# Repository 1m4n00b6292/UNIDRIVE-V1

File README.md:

# UNIDRIVE V1

A compact brushed DC motor driver board with encoder feedback, shunt current sensing and CAN bus, controlled by an **STM32G431KBU6**.

> ⚠️ **Status: hardware V1 done, firmware under development.**
> The firmware has not been checked on real hardware yet. Nothing in the firmware sections below should be read as tested or working.

## Overview

**UNIDRIVE** is a single-channel brushed DC motor driver built around the **TI DRV8701P** gate driver and an H-bridge made of 4 discrete N-channel MOSFETs. An **STM32G431KBU6** (Cortex-M4F, 170 MHz) handles the control. Feedback comes from:

- a **quadrature encoder** for speed and position
- a **5 mΩ low-side shunt** read through the DRV8701 current-sense amplifier

The board can be commanded over **CAN (FDCAN1)** or **UART**, and four status LEDs show its state.

The goal is a small, general-purpose driver for robotics and hobby projects, with duty, current, velocity and position control modes.

<!-- Fixed width, centered -->
<p align="center">
  
  <br>
  <em>Figure 1: PCB 3D view (top)</em>
</p>

## Main Components

### Hardware

| Part | Function |
|------|----------|
| STM32G431KBU6 (UFQFPN-32) + 24 MHz crystal | Main MCU (HSE → PLL 170 MHz) |
| DRV8701P | Brushed DC H-bridge gate driver (PWM IN1/IN2 variant) |
| 4 × N-channel MOSFET | Full H-bridge power stage |
| 5 mΩ shunt (R8) | Current sensing, read through the DRV8701 SO amplifier (gain 20 V/V) |
| Quadrature encoder (external) | Speed / position feedback (x4 decoding on TIM2) |
| TJA1051T/3 | CAN transceiver, with optional 120 Ω termination (JP2) |
| AP2112K-3.3 | 3.3 V LDO for the MCU |
| 4 LEDs | RUN / CAL / FAULT / COMM status |
| SWD header (J6) | Programming and debugging |

### Pin Map

| Signal | Pin | Peripheral | Notes |
|--------|-----|------------|-------|
| HSE OSC_IN / OSC_OUT | PF0 / PF1 | RCC | 24 MHz crystal |
| CSENSE (DRV8701 SO) | PA0 | ADC1_IN1 | Current-sense amplifier output |
| nFAULT | PA1 | GPIO / EXTI1 | Pull-up to DVDD, active low |
| IN1 / IN2 | PA2 / PA3 | TIM15_CH1 / CH2 | 20 kHz PWM |
| nSLEEP | PA4 | GPIO | Driver enable |
| UART TX / RX | PA9 / PA10 | USART1 | On header J5 |
| CAN RX / TX | PA11 / PA12 | FDCAN1 | To TJA1051T/3 |
| SWDIO / SWCLK | PA13 / PA14 | SWD | Header J6 |
| Encoder A / B | PA15 / PB3 | TIM2_CH1 / CH2 | 32-bit encoder counter |
| LED RUN / CAL / FAULT / COMM | PB4 / PB5 / PB6 / PB7 | GPIO | Active low |
| BOOT0 | PB8 | — | 10k to GND (boot from flash) |
| Expansion | PA5, PA6, PA7, PA8, PB0 | — | Free, on header J5 |

<!-- Fixed width, centered -->
<p align="center">
  
  <br>
  <em>Figure 2: Layout view (L1)</em>
</p>
<p align="center">
  
  <br>
  <em>Figure 3: Layout view (L2)</em>
</p>
<p align="center">
  
  <br>
  <em>Figure 4: Layout view (L3)</em>
</p>
<p align="center">
  
  <br>
  <em>Figure 5: Layout view (L4)</em>
</p>

### Connectors

| Connector | Pinout |
|-----------|--------|
| **J1** (1×12) | 1/3 CANL, 2/4 CANH, 5 VENC, 6 ENCA, 7 ENCB, 8 GND, 9 M−, 10 M+, 11 GND, 12 VCC (power input) |
| **J2** (1×3) | Encoder supply select: +5 V (1-2) or +3.3 V (2-3) |
| **J5** (2×4) | PA9 (TX), PA10 (RX), GND, PA8, PB0, PA7, PA6, PA5 |
| **J6** (1×3) | SWDIO, SWCLK, GND |

> **JP1** connects the TJA1051 VIO pin to +3.3 V. It is an **open** solder jumper by default and **must be bridged** for CAN to work.
> **JP2** enables the 120 Ω CAN termination. Bridge it only on the boards at the ends of the bus.

### Driver Logic (DRV8701P)

| IN1 | IN2 | Bridge state |
|-----|-----|--------------|
| 0 | 0 | Coast (Hi-Z) |
| 1 | 0 | Forward |
| 0 | 1 | Reverse |
| 1 | 1 | Brake (low-side slow decay) |

- Current scaling: `I ≈ (V_SO − 0.05 V) / (0.005 Ω × 20)` ≈ **10 A/V**
- The SO output is valid only while the bridge is driving, not during brake or coast.
- Hardware current chopping limit: VREF ≈ 2.09 V → about **20 A**

## Firmware

> 🚧 **Under development.** The firmware structure and features below are the design target. They have been written and partly simulated on a PC, but **not yet confirmed on the real board**.

The firmware is built with **STM32CubeMX + CMake + STM32 HAL (G4)**. CubeMX generates the pin setup and peripheral init. All application code is in `App/`, and `main.c` only calls `app_init()` and `app_update()`.

### Planned Software Modules

| Layer / File | Description | Status |
|--------------|-------------|--------|
| `App/config.h` | Single place for every tunable value (PWM frequency, gains, limits, motor model) | 🚧 In progress |
| `App/bsp/` | Low-level peripheral drivers: GPIO/LEDs, TIM15 PWM, ADC + DMA, TIM2 encoder, TIM6 tick, USART1 DMA, FDCAN | 🚧 Written, not verified on hardware |
| `App/sensor/current` | Shunt current measurement synced to the PWM, offset calibration, filtering, overcurrent detection | 🚧 Written, not verified on hardware |
| `App/sensor/encoder` | Position (64-bit) and velocity estimation (PLL observer) | 🚧 Written, not verified on hardware |
| `App/sensor/monitor` | VDDA and MCU temperature monitoring | 🚧 Written, not verified on hardware |
| `App/control/drv8701` | Driver state machine: sleep / wake / ready / fault handling | 🚧 Written, not verified on hardware |
| `App/control/hbridge` | Duty → DRV8701P switching pattern, ADC sample timing | 🚧 Written, not verified on hardware |
| `App/control/pid`, `profile` | PID controller (ported from VIXULY), trapezoidal motion profile | 🚧 Written, not verified on hardware |
| `App/control/control` | Control loops: duty, current, velocity and position modes, fault handling | 🚧 Written, not verified on hardware |
| `App/app/` | State machine, CLI, telemetry, CAN protocol, parameter storage in flash | ⏳ Not started |

### Planned Features

- [ ] Control modes: **OFF / BRAKE / DUTY / CURRENT / VELOCITY / POSITION**
- [ ] 20 kHz PWM with current sampling locked to the PWM period
- [ ] Velocity PID with feed-forward and setpoint ramp
- [ ] Position control with a trapezoidal motion profile
- [ ] Software overcurrent, stall, following-error and over-temperature protection
- [ ] DRV8701 fault handling (nFAULT)
- [ ] UART command line and telemetry
- [ ] CAN protocol with node addressing
- [ ] Parameter storage in flash

### Development Progress

- [x] Schematic and PCB (V1)
- [x] Pin map and peripheral plan
- [x] Firmware architecture
- [x] Low-level drivers and control code written
- [x] Control logic tested in a PC simulation (motor + bridge + encoder model)
- [ ] **Board bring-up on real hardware**
- [ ] Current-sense calibration on hardware
- [ ] PID tuning on a real motor
- [ ] Application layer (CLI, CAN protocol, flash parameters)

## Quick User Guide

> The steps below describe the intended workflow. They may change as the firmware develops.

### 1. Build and flash

1. Open the firmware project (CMake, generated by STM32CubeMX).
2. Review `App/config.h`, especially the motor model, encoder resolution and current limits.
3. Build and flash through the **SWD header (J6)** with an ST-Link or a similar probe.

### 2. Hardware setup

1. Bridge **JP1** if you want to use CAN.
2. Set **J2** to match your encoder supply voltage (5 V or 3.3 V).
3. Connect the motor to **M+ / M−**, the encoder to **ENCA / ENCB / VENC / GND**, and the supply to **VCC / GND** on J1.
4. Connect a USB-UART adapter to **J5** (PA9 TX, PA10 RX, GND) for the debug terminal.

### 3. Run

🚧 *Under development: the command interface and CAN protocol are not finished yet.*

## Known Issues (Hardware V1)

- **CAN:** JP1 is open by default, so CAN does not work until it is bridged.
- **nFAULT:** the pull-up goes to DVDD, which is off in sleep, so nFAULT reads low while the driver sleeps. The firmware has to ignore it while asleep and during wake-up.
- **PA0 input range:** the SO output can swing up to about 4.8 V during an overload, which is above the 3.6 V limit of PA0. A series resistor or clamp is recommended in the next revision.
- **Net names:** "IN1/EN" and "IN2/PH" are misleading. The DRV8701**P** only has the PWM (IN1/IN2) mode. Select DRV8701**E** variant for PH/EN mode.
- **Missing sensing:** there is no bus voltage or board temperature sense going to the MCU.
- **Current measurement limits:** current can't be measured below about 10 % duty, or during brake or coast (a limit of the low-side, unidirectional sense amplifier).

## Repository Structure

```text
UNIDRIVE-V1/
├── Hardware/
│   └── (KiCad schematic and PCB files)
├── Firmware/
│   ├── Core/              # CubeMX generated
│   ├── Drivers/           # STM32 HAL
│   ├── App/
│   │   ├── config.h
│   │   ├── bsp/
│   │   ├── sensor/
│   │   ├── control/
│   │   └── app/
│   ├── UNIDRIVE_FW.ioc
│   └── CMakeLists.txt
├── docs/
└── README.md
```

## Author
[@1m4n00b6292](https://github.com/1m4n00b6292)

## License

This project is licensed under the [MIT License](LICENSE).

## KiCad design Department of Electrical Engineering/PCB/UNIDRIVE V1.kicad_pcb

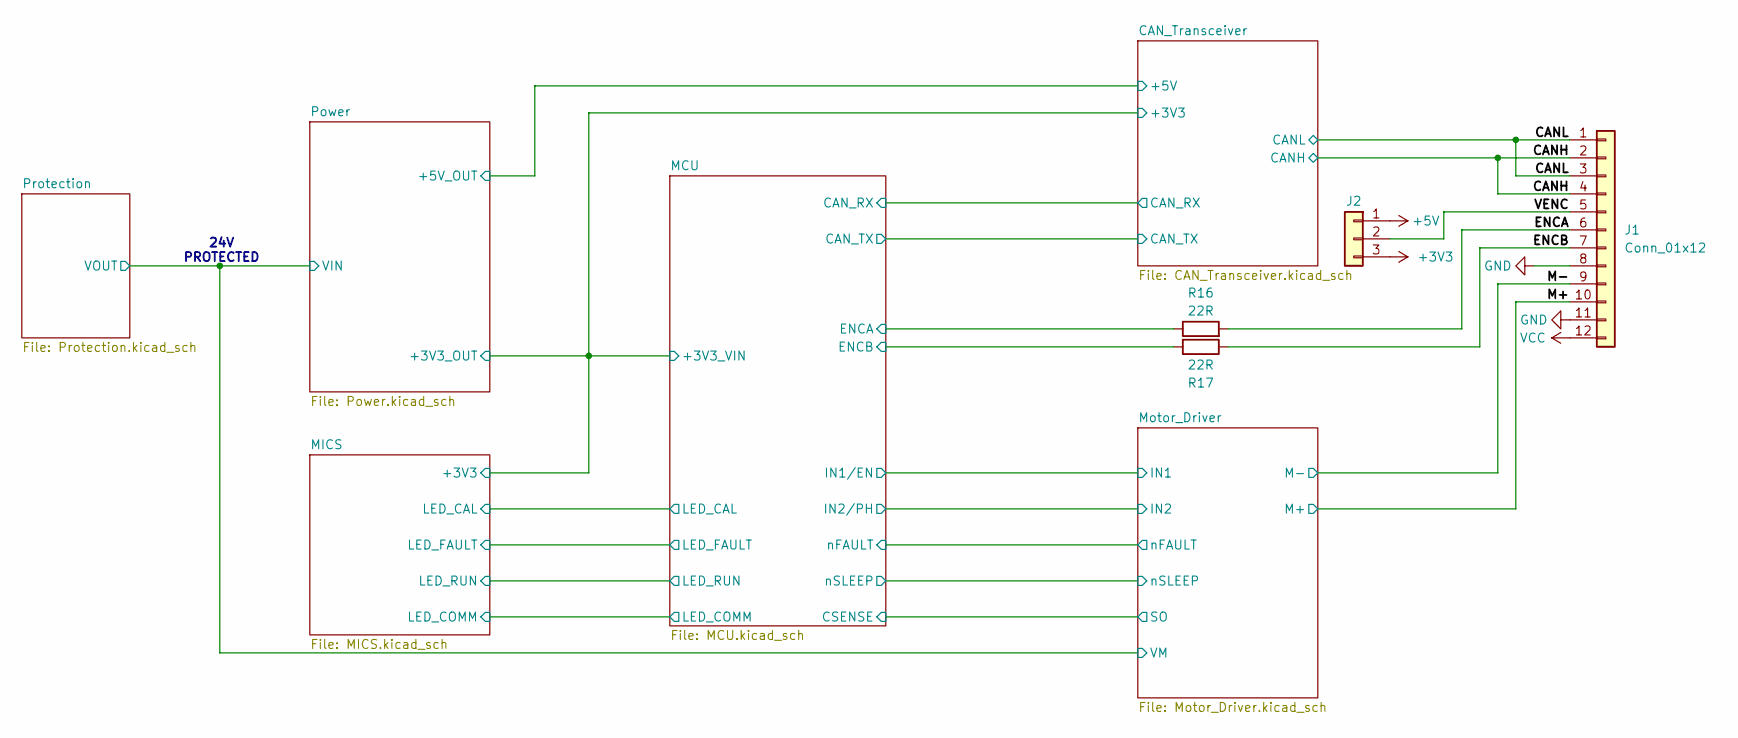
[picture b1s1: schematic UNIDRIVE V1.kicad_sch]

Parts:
J1: Conn_01x12; PhoenixContact_MSTBA_2,5_12-G-5,08_1x12_P5.08mm_Horizontal
J2: Conn_01x03; PinHeader_1x03_P2.54mm_Vertical
R16, R17: 22R; R_0603_1608Metric_Pad0.98x0.95mm_HandSolder

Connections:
+3V3: J2.3; also elsewhere on the board
+5V: J2.1; also elsewhere on the board
/CANH: J1.2, J1.4; also elsewhere on the board
/CANL: J1.1, J1.3; also elsewhere on the board
/ENCA: J1.6, R16.2
/ENCB: J1.7, R17.1
/M+: J1.10; also elsewhere on the board
/M-: J1.9; also elsewhere on the board
/MCU/PA15: R16.1; also elsewhere on the board
/MCU/PB3: R17.2; also elsewhere on the board
/VENC: J1.5, J2.2
GND: J1.8, J1.11; also elsewhere on the board
VCC: J1.12; also elsewhere on the board

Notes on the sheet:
24V PROTECTED

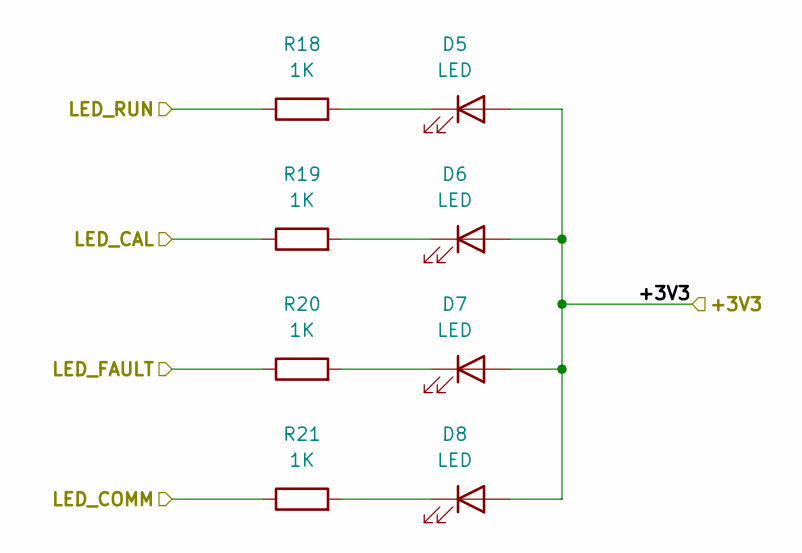
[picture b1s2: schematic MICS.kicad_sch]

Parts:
D5, D6, D7, D8: LED; LED_1206_3216Metric
R18, R19, R20, R21: 1K; R_0603_1608Metric_Pad0.98x0.95mm_HandSolder

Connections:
+3V3: D5.2 (A), D6.2 (A), D7.2 (A), D8.2 (A); also elsewhere on the board
/MCU/PB4: R18.1; also elsewhere on the board
/MCU/PB5: R19.1; also elsewhere on the board
/MCU/PB6: R20.1; also elsewhere on the board
/MCU/PB7: R21.1; also elsewhere on the board
unnamed: D5.1 (K), R18.2
unnamed: D6.1 (K), R19.2
unnamed: D7.1 (K), R20.2
unnamed: D8.1 (K), R21.2

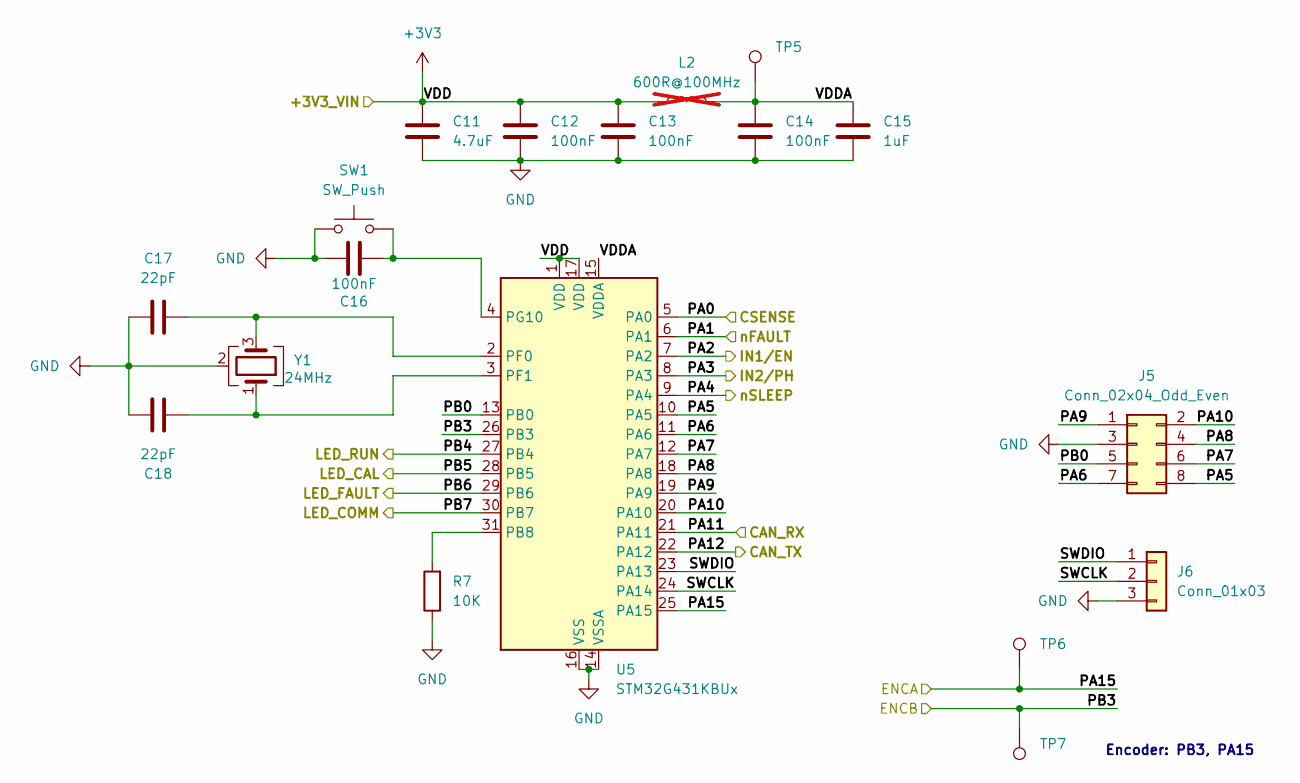
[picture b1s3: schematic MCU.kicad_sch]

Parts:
C11: 4.7uF; C_0603_1608Metric_Pad1.08x0.95mm_HandSolder
C12, C13, C14, C16: 100nF; C_0603_1608Metric_Pad1.08x0.95mm_HandSolder
C15: 1uF; C_0603_1608Metric_Pad1.08x0.95mm_HandSolder
C17, C18: 22pF; C_0603_1608Metric_Pad1.08x0.95mm_HandSolder
J5: Conn_02x04_Odd_Even; PinHeader_2x04_P2.54mm_Vertical
J6: Conn_01x03; PinHeader_1x03_P2.54mm_Vertical
L2: 600R@100MHz; L_0805_2012Metric_Pad1.05x1.20mm_HandSolder; not fitted
R7: 10K; R_0603_1608Metric_Pad0.98x0.95mm_HandSolder
SW1: SW_Push; SW_SPST_CK_RS282G05A3
TP5, TP6, TP7: TestPoint; TestPoint_Pad_D1.0mm
U5: STM32G431KBUx; QFN-32-1EP_5x5mm_P0.5mm_EP3.45x3.45mm
Y1: 24MHz; Crystal_SMD_3225-4Pin_3.2x2.5mm

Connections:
+3V3: C11.1, C12.1, C13.1, L2.1, U5.1 (VDD), U5.17 (VDD); also elsewhere on the board
/CAN_Transceiver/CAN_RX: U5.21 (PA11); also elsewhere on the board
/CAN_Transceiver/CAN_TX: U5.22 (PA12); also elsewhere on the board
/MCU/PA0: U5.5 (PA0); also elsewhere on the board
/MCU/PA1: U5.6 (PA1); also elsewhere on the board
/MCU/PA2: U5.7 (PA2); also elsewhere on the board
/MCU/PA3: U5.8 (PA3); also elsewhere on the board
/MCU/PA4: U5.9 (PA4); also elsewhere on the board
/MCU/PA5: J5.8, U5.10 (PA5)
/MCU/PA6: J5.7, U5.11 (PA6)
/MCU/PA7: J5.6, U5.12 (PA7)
/MCU/PA8: J5.4, U5.18 (PA8)
/MCU/PA9: J5.1, U5.19 (PA9)
/MCU/PA10: J5.2, U5.20 (PA10)
/MCU/PA15: TP6.1 (1_1), U5.25 (PA15); also elsewhere on the board
/MCU/PB0: J5.5, U5.13 (PB0)
/MCU/PB3: TP7.1 (1_1), U5.26 (PB3); also elsewhere on the board
/MCU/PB4: U5.27 (PB4); also elsewhere on the board
/MCU/PB5: U5.28 (PB5); also elsewhere on the board
/MCU/PB6: U5.29 (PB6); also elsewhere on the board
/MCU/PB7: U5.30 (PB7); also elsewhere on the board
/MCU/SWCLK: J6.2, U5.24 (PA14)
/MCU/SWDIO: J6.1, U5.23 (PA13)
/MCU/VDDA: C14.1, C15.1, L2.2, TP5.1 (1_1), U5.15 (VDDA)
GND: C11.2, C12.2, C13.2, C14.2, C15.2, C16.1, C17.2, C18.2, J5.3, J6.3, R7.1, SW1.1, U5.14 (VSSA), U5.16 (VSS), U5.32 (VSS), U5.33 (VSS), Y1.2 (G), Y1.4 (G); also elsewhere on the board
unnamed: R7.2, U5.31 (PB8)
unnamed: C17.1, U5.2 (PF0), Y1.3
unnamed: C18.1, U5.3 (PF1), Y1.1
unnamed: C16.2, SW1.2, U5.4 (PG10)

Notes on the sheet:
Encoder: PB3, PA15

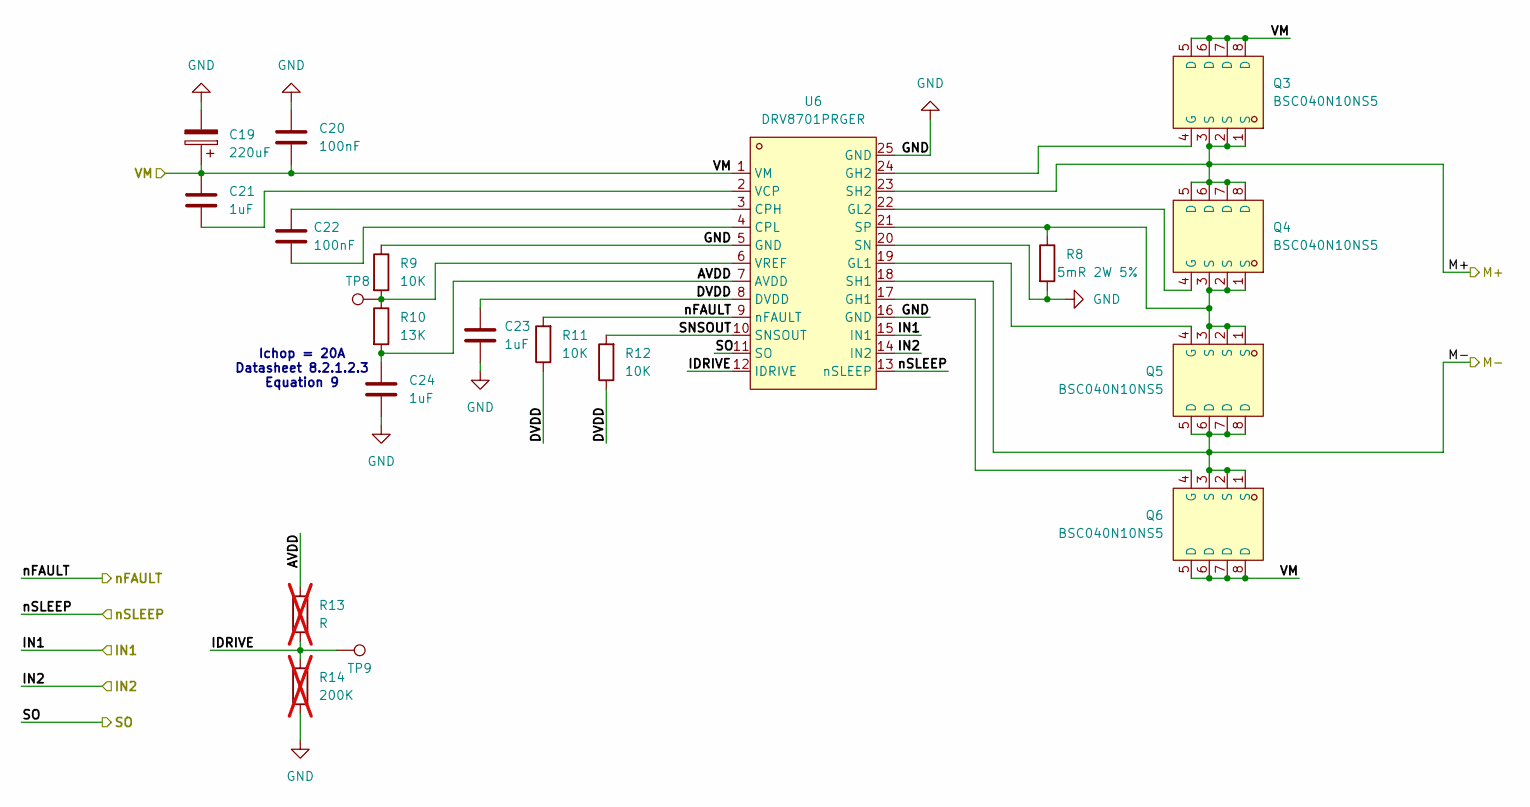
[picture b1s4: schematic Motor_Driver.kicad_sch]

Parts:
C19: 220uF; CP_Elec_6.3x7.7
C20, C22: 100nF; C_0603_1608Metric_Pad1.08x0.95mm_HandSolder
C21, C23, C24: 1uF; C_0603_1608Metric_Pad1.08x0.95mm_HandSolder
Q3, Q4, Q5, Q6: BSC040N10NS5; PG-TDSON-8_L5.9-W5.1-P1.27-LS6.1-BL; MPN BSC040N10NS5; LCSC Part C534334
R8: 5mR 2W 5%; R_2512_6332Metric; MPN FRM252WJR005TN; LCSC C7467241
R9, R11, R12: 10K; R_0603_1608Metric_Pad0.98x0.95mm_HandSolder
R10: 13K; R_0603_1608Metric_Pad0.98x0.95mm_HandSolder
R13: R; R_0603_1608Metric_Pad0.98x0.95mm_HandSolder; not fitted
R14: 200K; R_0603_1608Metric_Pad0.98x0.95mm_HandSolder; not fitted
TP8, TP9: TestPoint; TestPoint_Pad_D1.0mm
U6: DRV8701PRGER; VQFN-24_L4.0-W4.0-P0.50-BL-EP2.8; MPN DRV8701PRGER; LCSC Part C114178

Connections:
/M+: Q3.1 (S), Q3.2 (S), Q3.3 (S), Q4.5 (D), Q4.6 (D), Q4.7 (D), Q4.8 (D), U6.23 (SH2); also elsewhere on the board
/M-: Q5.5 (D), Q5.6 (D), Q5.7 (D), Q5.8 (D), Q6.1 (S), Q6.2 (S), Q6.3 (S), U6.18 (SH1); also elsewhere on the board
/MCU/PA0: U6.11 (SO); also elsewhere on the board
/MCU/PA1: R11.2, U6.9 (nFAULT); also elsewhere on the board
/MCU/PA2: U6.15 (IN1); also elsewhere on the board
/MCU/PA3: U6.14 (IN2); also elsewhere on the board
/MCU/PA4: U6.13 (nSLEEP); also elsewhere on the board
/Motor_Driver/AVDD: C24.1, R10.2, R13.2, U6.7 (AVDD)
/Motor_Driver/DVDD: C23.1, R11.1, R12.1, U6.8 (DVDD)
/Motor_Driver/IDRIVE: R13.1, R14.2, TP9.1 (1_1), U6.12 (IDRIVE)
/Motor_Driver/SNSOUT: R12.2, U6.10 (SNSOUT)
/Motor_Driver/VM: C19.1, C20.2, C21.1, Q3.5 (D), Q3.6 (D), Q3.7 (D), Q3.8 (D), Q6.5 (D), Q6.6 (D), Q6.7 (D), Q6.8 (D), U6.1 (VM); also elsewhere on the board
GND: C19.2, C20.1, C23.2, C24.2, R8.2, R9.1, R14.1, U6.5 (GND), U6.16 (GND), U6.20 (SN), U6.25 (GND); also elsewhere on the board
unnamed: Q3.4 (G), U6.24 (GH2)
unnamed: Q4.4 (G), U6.22 (GL2)
unnamed: Q5.4 (G), U6.19 (GL1)
unnamed: Q6.4 (G), U6.17 (GH1)
unnamed: C22.1, U6.3 (CPH)
unnamed: C22.2, U6.4 (CPL)
unnamed: Q4.1 (S), Q4.2 (S), Q4.3 (S), Q5.1 (S), Q5.2 (S), Q5.3 (S), R8.1, U6.21 (SP)
unnamed: C21.2, U6.2 (VCP)
unnamed: R9.2, R10.1, TP8.1 (1_1), U6.6 (VREF)

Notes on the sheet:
Ichop = 20A Datasheet 8.2.1.2.3 Equation 9

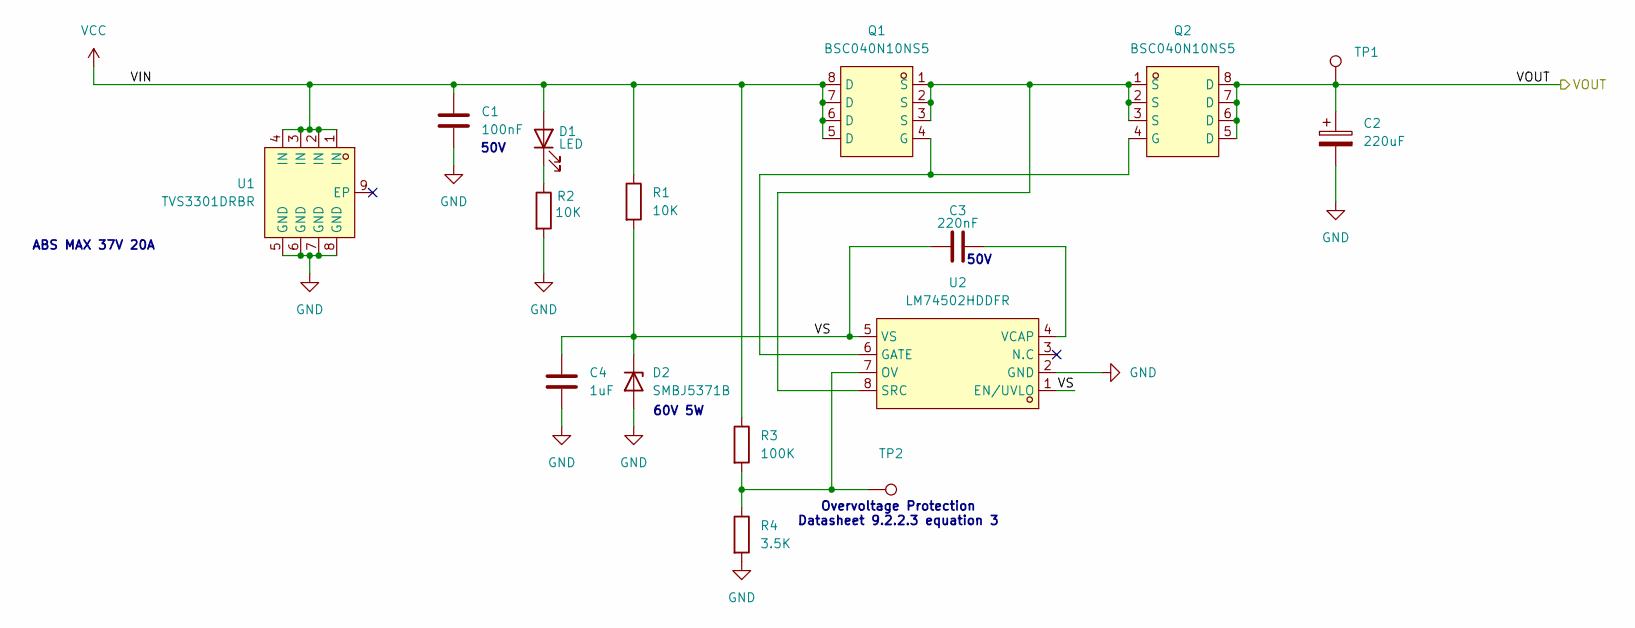
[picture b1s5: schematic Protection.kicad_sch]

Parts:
C1: 100nF; C_1206_3216Metric
C2: 220uF; CP_Radial_D13.0mm_P5.00mm
C3: 220nF; C_0603_1608Metric_Pad1.08x0.95mm_HandSolder
C4: 1uF; C_1206_3216Metric
D1: LED; LED_1206_3216Metric
D2: SMBJ5371B; D_SMB_Handsoldering
Q1, Q2: BSC040N10NS5; PG-TDSON-8_L5.9-W5.1-P1.27-LS6.1-BL; MPN BSC040N10NS5; LCSC Part C534334
R1, R2: 10K; R_1206_3216Metric
R3: 100K; R_0603_1608Metric_Pad0.98x0.95mm_HandSolder
R4: 3.5K; R_0603_1608Metric_Pad0.98x0.95mm_HandSolder
TP1, TP2: TestPoint; TestPoint_Pad_D1.0mm
U1: TVS3301DRBR; VSON-8_L3.0-W3.0-P0.65-BL-EP; MPN TVS3301DRBR; LCSC Part C2864392
U2: LM74502HDDFR; SOT-23-8_L2.9-W1.6-P0.65-LS2.8-BL; MPN LM74502HDDFR; LCSC Part C5219202

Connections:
/Motor_Driver/VM: C2.1, Q2.5 (D), Q2.6 (D), Q2.7 (D), Q2.8 (D), TP1.1 (1_1); also elsewhere on the board
/Protection/VS: C3.1, C4.1, D2.1 (K), R1.2, U2.1 (EN/UVLO), U2.5 (VS)
GND: C1.2, C2.2, C4.2, D2.2 (A), R2.2, R4.2, U1.5 (GND), U1.6 (GND), U1.7 (GND), U1.8 (GND), U2.2 (GND); also elsewhere on the board
unnamed: D1.1 (K), R2.1
unnamed: Q1.4 (G), Q2.4 (G), U2.6 (GATE)
unnamed: R3.2, R4.1, TP2.1 (1_1), U2.7 (OV)
unnamed: Q1.1 (S), Q1.2 (S), Q1.3 (S), Q2.1 (S), Q2.2 (S), Q2.3 (S), U2.8 (SRC)
unnamed: C3.2, U2.4 (VCAP)
VCC: C1.1, D1.2 (A), Q1.5 (D), Q1.6 (D), Q1.7 (D), Q1.8 (D), R1.1, R3.1, U1.1 (IN), U1.2 (IN), U1.3 (IN), U1.4 (IN); also elsewhere on the board

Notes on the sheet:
60V 5W
ABS MAX 37V 20A
Overvoltage Protection Datasheet 9.2.2.3 equation 3
50V

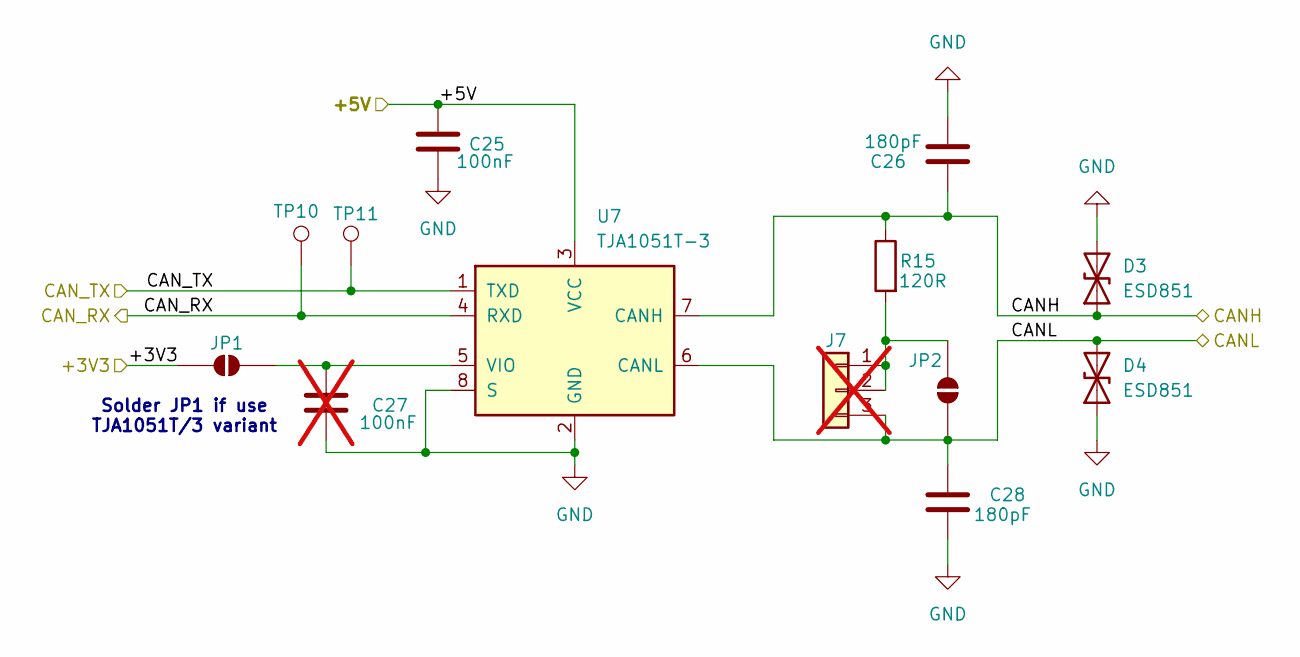
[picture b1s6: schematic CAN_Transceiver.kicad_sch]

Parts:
C25: 100nF; C_0603_1608Metric_Pad1.08x0.95mm_HandSolder
C26, C28: 180pF; C_0603_1608Metric_Pad1.08x0.95mm_HandSolder
C27: 100nF; C_0603_1608Metric_Pad1.08x0.95mm_HandSolder; not fitted
D3, D4: ESD851; D_SOD-323_HandSoldering
J7: Conn_01x03; PinHeader_1x03_P2.54mm_Vertical; not fitted
JP1, JP2: SolderJumper_2_Open; SolderJumper-2_P1.3mm_Open_TrianglePad1.0x1.5mm
R15: 120R; R_0603_1608Metric_Pad0.98x0.95mm_HandSolder
TP10, TP11: TestPoint; TestPoint_Pad_D1.0mm
U7: TJA1051T-3; SOIC-8_3.9x4.9mm_P1.27mm

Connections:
+3V3: JP1.2 (B); also elsewhere on the board
+5V: C25.1, U7.3 (VCC); also elsewhere on the board
/CANH: C26.1, D3.1 (A1), R15.1, U7.7 (CANH); also elsewhere on the board
/CANL: C28.1, D4.2 (A2), J7.3, JP2.2 (B), U7.6 (CANL); also elsewhere on the board
/CAN_Transceiver/CAN_RX: TP10.1 (1_1), U7.4 (RXD); also elsewhere on the board
/CAN_Transceiver/CAN_TX: TP11.1 (1_1), U7.1 (TXD); also elsewhere on the board
GND: C25.2, C26.2, C27.2, C28.2, D3.2 (A2), D4.1 (A1), U7.2 (GND), U7.8 (S); also elsewhere on the board
unnamed: J7.1, J7.2, JP2.1 (A), R15.2
unnamed: C27.1, JP1.1 (A), U7.5 (VIO)

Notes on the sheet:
Solder JP1 if use TJA1051T/3 variant

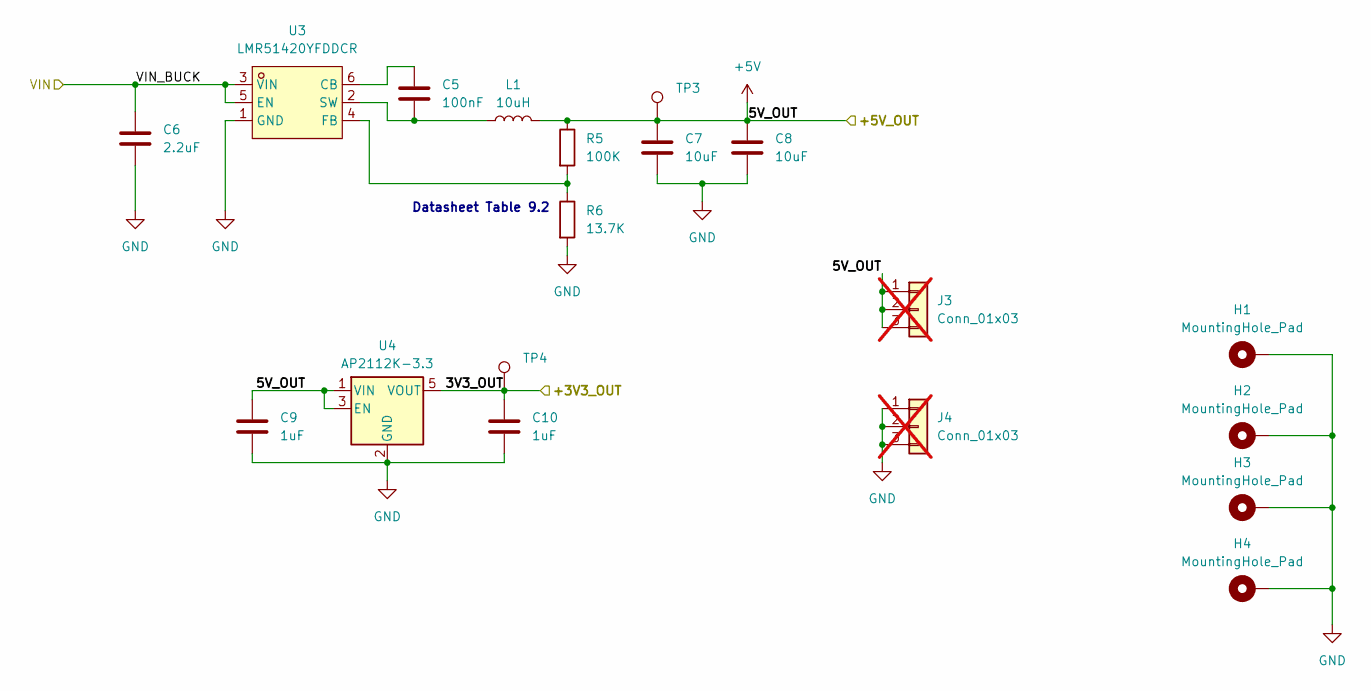
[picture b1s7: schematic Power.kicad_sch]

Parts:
C5: 100nF; C_0603_1608Metric_Pad1.08x0.95mm_HandSolder
C6: 2.2uF; C_0603_1608Metric_Pad1.08x0.95mm_HandSolder
C7, C8: 10uF; C_1206_3216Metric_Pad1.33x1.80mm_HandSolder
C9, C10: 1uF; C_1206_3216Metric_Pad1.33x1.80mm_HandSolder
H1, H2, H3, H4: MountingHole_Pad; MountingHole_3.2mm_M3_Pad_TopBottom
J3, J4: Conn_01x03; PinHeader_1x03_P2.54mm_Vertical; not fitted
L1: 10uH; L_Vishay_IHLP-1616
R5: 100K; R_0603_1608Metric_Pad0.98x0.95mm_HandSolder
R6: 13.7K; R_0603_1608Metric_Pad0.98x0.95mm_HandSolder
TP3, TP4: TestPoint; TestPoint_Pad_D1.0mm
U3: LMR51420YFDDCR; SOT-23-6_L2.9-W1.6-P0.95-LS2.8-BL; MPN LMR51420YFDDCR; LCSC Part C7296200
U4: AP2112K-3.3; SOT-23-5

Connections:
+3V3: C10.1, TP4.1 (1_1), U4.5 (VOUT); also elsewhere on the board
+5V: C7.1, C8.1, C9.1, J3.1, J3.2, J3.3, L1.2, R5.1, TP3.1 (1_1), U4.1 (VIN), U4.3 (EN); also elsewhere on the board
/Motor_Driver/VM: C6.1, U3.3 (VIN), U3.5 (EN); also elsewhere on the board
GND: C6.2, C7.2, C8.2, C9.2, C10.2, H1.1 (1_1), H2.1 (1_1), H3.1 (1_1), H4.1 (1_1), J4.1, J4.2, J4.3, R6.2, U3.1 (GND), U4.2 (GND); also elsewhere on the board
unnamed: C5.1, U3.6 (CB)
unnamed: R5.2, R6.1, U3.4 (FB)
unnamed: C5.2, L1.1, U3.2 (SW)

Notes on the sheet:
Datasheet Table 9.2

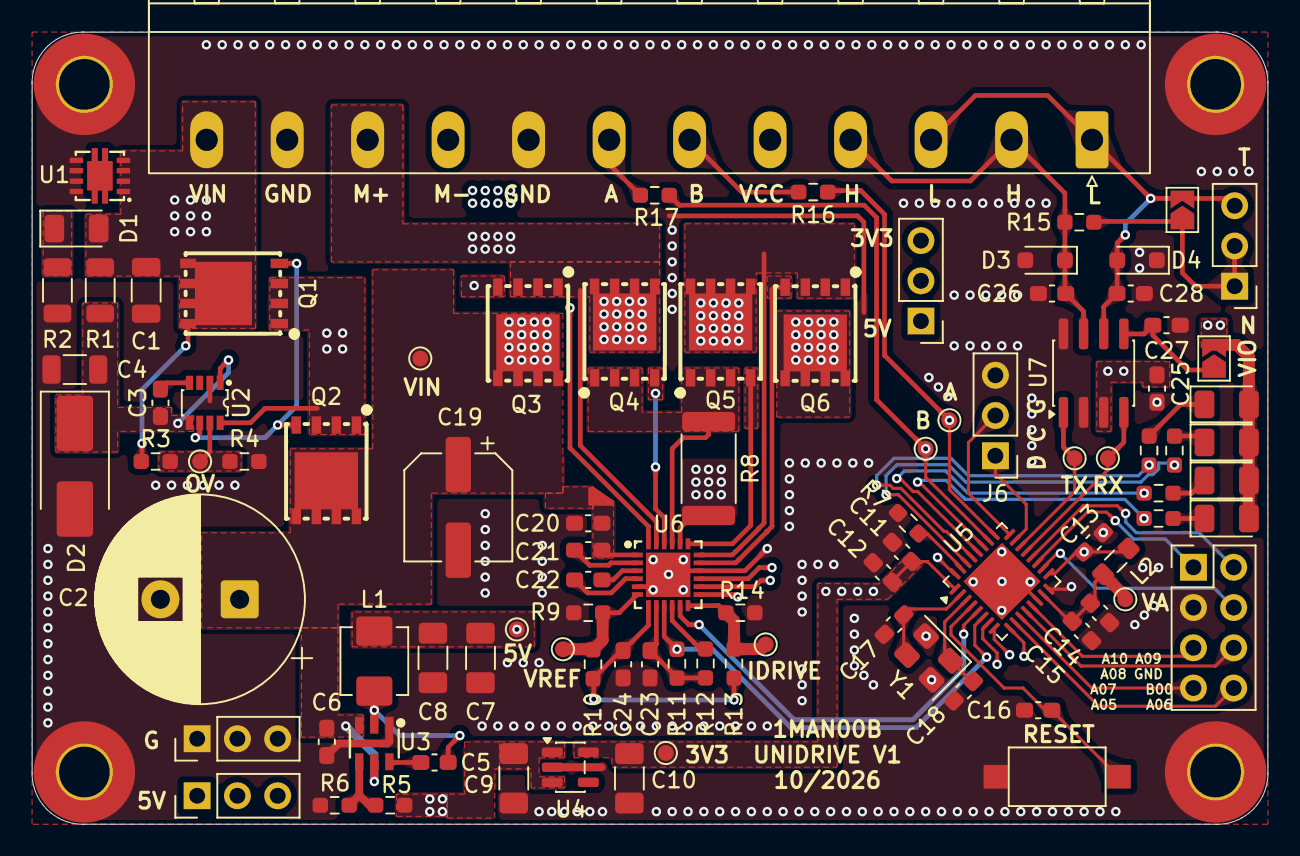
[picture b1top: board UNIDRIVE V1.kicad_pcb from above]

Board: 4 copper layers, 78.0 x 50.0 mm, 98 parts (0 on the bottom side), 67 nets.
